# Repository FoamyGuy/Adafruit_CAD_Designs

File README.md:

# Adafruit_CAD_Designs
STEP, 3MF, GIF, JPG, other design files, and README.md for accessories, cases, and mounts that fit Adafruit boards but are not sold in the Adafruit Store

Each board has a folder named `PID Board`, using its Adafruit product ID, with one subfolder per design, e.g. `6200 Fruit Jam/Light Tunnel`. A design that fits several boards lives under one of them, and its README lists the others.

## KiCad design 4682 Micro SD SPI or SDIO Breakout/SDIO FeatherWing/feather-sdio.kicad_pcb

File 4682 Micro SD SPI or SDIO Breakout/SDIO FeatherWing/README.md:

# Micro SD Breakout SDIO FeatherWing

A FeatherWing that holds an [Adafruit Micro SD SPI or SDIO Card Breakout](https://www.adafruit.com/product/4682) and wires its 4-bit SDIO bus to the Feather, so you can test SDIO without a breadboard.

## Files

| File | What |
|---|---|
| `.step` | Board with headers, for any CAD tool |
| `.3mf` | Board mesh, for test fits |
| `feather-sdio.kicad_pro`, `.kicad_sch`, `.kicad_pcb` | KiCad source |

## Parts

| Part | Qty |
|---|---|
| 1x16 and 1x12 male headers | 1 each |
| 1x09 female socket, SMD | 1 |

Source: [mikeysklar/feather-sdio](https://github.com/mikeysklar/feather-sdio)

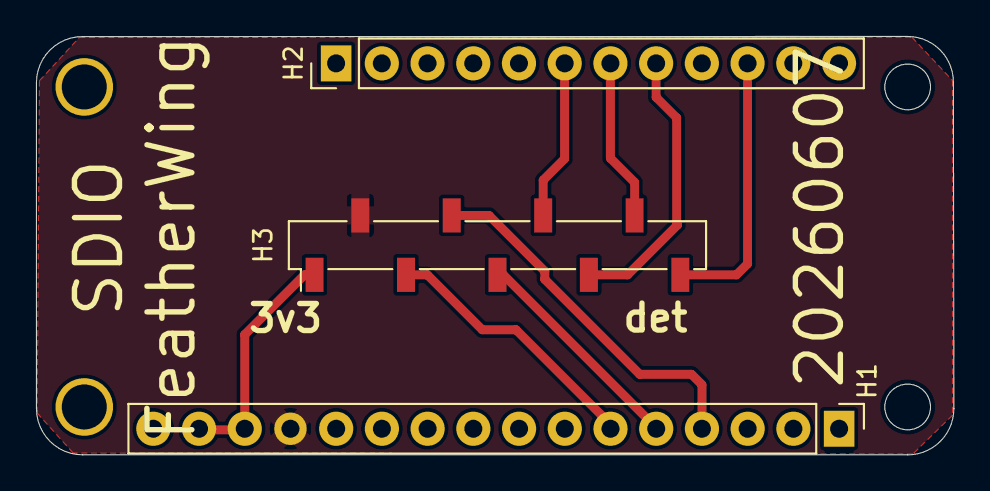
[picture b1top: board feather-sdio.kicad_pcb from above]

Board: 2 copper layers, 51.0 x 23.2 mm, 3 parts (0 on the bottom side), 9 nets.

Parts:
H1: HEADER-1X16ROUND; PinHeader_1x16_P2.54mm_Vertical
H2: HEADER-1X12; PinHeader_1x12_P2.54mm_Vertical
H3: Conn_01x09_Socket; PinSocket_1x09_P2.54mm_Vertical_SMD_Pin1Left

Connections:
3v3: H1.14, H1.15, H3.1
/clock: H1.6, H3.3
/cmd: H1.5, H3.5
/data0: H1.4, H3.4
/data1: H2.8, H3.7
/data2: H2.7, H3.8
/data3: H2.6, H3.6
/det: H2.10, H3.9
gnd: H1.13, H3.2
